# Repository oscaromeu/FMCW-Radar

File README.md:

# Advise

The FMCW radar project is a very exciting project but it has many difficulties. First of
all, it is a project that requires a long time since it involves many aspects of electrical engineering and takes many steps to build a prototype. Ideally, you should start with a modular approach, test all the modules
separately and then join them in a final design. To carry out this project ideally it should be done between three people in this way the signal processing part could be included. RF is a very exciting field but depending the project doing at your home will be very difficult because as we rise the frequency the equipment gets very expensive. If you want to make a Radar or do some stuff related to radio frequency: SDR, Radio Receivers/Transmitters, Antennas, ...  take a look at the following sources:

+ [University of California EEC134](https://github.com/ucdart/UCD-EEC134)
+ [Third version of homemade 6 GHz FMCW Radar](https://hforsten.com/third-version-of-homemade-6-ghz-fmcw-radar.html)
+ [ARRL Handbook](http://www.arrl.org/arrl-handbook-2019)

This repo is for remember myself that I was able to make a radar with the aid of my bachelor thesis supervisor. Thank you Javier, this project would not have been the same without your wisdom and your hands on expertise. :)

# FMCW-RADAR Project

The primary purpose of this project was to design and implement an Frequency Modulated Continous Wave Radar (FMCW) system centered at 5.8 GHz which can perform range, Doppler,
and synthetic aperture radar (SAR) measurements. The project was done with a modular design
approach and it had the following deliverables

+ RF front end board
+ Tx/Rx Antennas both Vivaldi type

## Target Audience 

The target audience of this project encompasses educational institutions or any individual
afiliated or not to any educational institution. All of the outputs of the project has a MIT License and are avaible at github. 

## Architecture general overview

A homodyne receiver is selected due to its small size and low parts count. In the following figure we
have a basic diagram of the radar system. In green we have the transmitter path and in red
we have the receiver path.

img//experimental-setup-1.jpg
## General overview of the results

### Vivaldi Antenna

Usually radars use very directional horn antennas. Directionality of the beam is important
so that only signal from the target is picked up instead of the surroundings. Besides the
directionality radar antenna should have low sidebands so that antenna to antenna coupling
is low and it doesn’t pick up reflected signals from behind and sides of the radar. 
Maybe a pyramidal horn antenna would be a good choice it can fulfill all the specifications
but it has high cost. Another option was Patch antenna but it was discarted due to it has a
low fractional bandwidth.
Finally, we decided to made a Vivaldi antenna. Vivaldi antennas are useful for any frequency, as all antennas are scalable in size for use at any frequency. Printed circuit technology
makes this type antenna cost effective at microwave frequencies exceeding 1 GHz.

The substrate of the antenna vivaldi was chosen
as a low cost FR4 material of thickness 1.2 mm. This was an error since the simulation was
done with a thickness of 0.8mm. The third antenna was fabricated with a thickness of 0.8mm. For this antenna the experimental data fits better with the simulation.

### Bottom 

### Top

### Experimental Results compared with simulation ones.

</br> </br> 
As we can see in the previous figure the reflection coefficient at the input relative to 50-ohm reference
impedance is below -10 dB for the frequency range from 3.1 GHz to 11 GHz.

## Radar board results

The radar test board is the last step of the test phase.  Prior to that a modular test approach was followed to verify that every component of the radar worked as expected. In the following figure is shown the final PCB of the radar system. In this stage it was encountered that the footprint of the VCO was not correct. Due to this the test applied to the radar was difficult
and hence the results are poor.

## Experimental Results 

</br> </br>

</br> </br>

####  A. Spectrum of the output signal before going to the transmitter antenna

#### B. Spectrum of the output of the mixer

The output of the Mixer is shown in Figure B. As is shown the baseband spectrum is
centered approximately at 44MHz and it has -22dB of power. This signal was acquired directly
with the aid of an active probe at the output of the Mixer. The signal that was being sent
with transmitter antenna is shown in Figure A.

## Some Future Ideas

+ Change the center frequency of 5GHz to 2.4GHz. 
+ Change the Wilkinson Divider for Coupler divider design. This could give us the flexibility to redistribute the power.
+ A 4 layer layout design is better option to design the radar since this way we separate
the signal layer with power and ground layer.
+ Process the IF signal with the aid of a microcontroller. Before processing the signal 
with a microcontroller a base band signal board has to be done in order to accomodate
the signal to the input ADC of the microcontroller.

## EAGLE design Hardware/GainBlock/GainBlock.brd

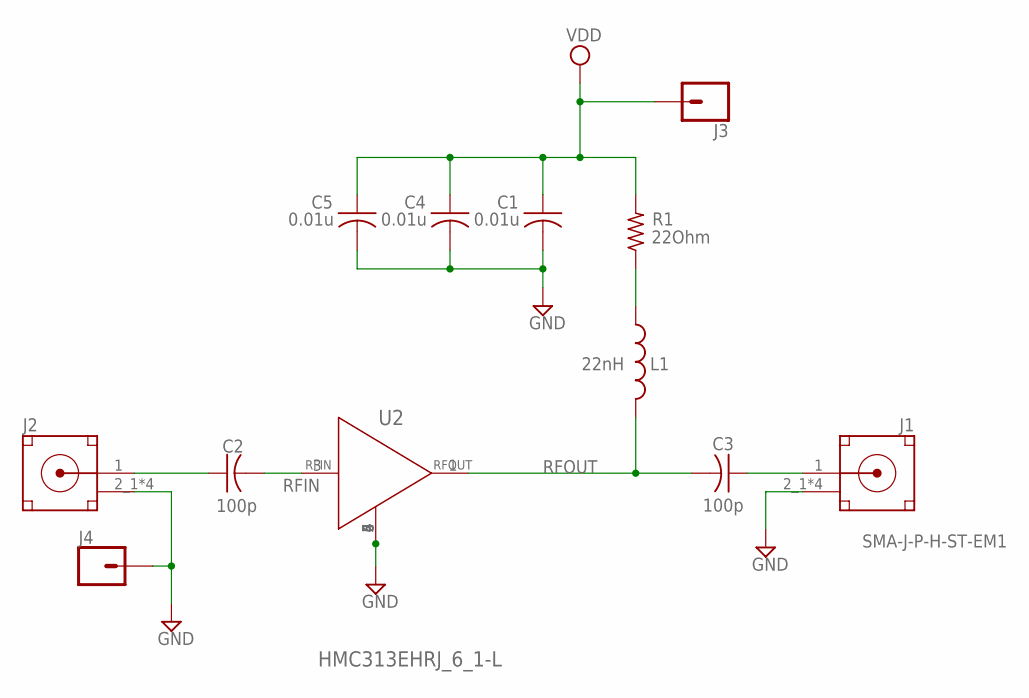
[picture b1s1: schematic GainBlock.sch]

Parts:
C1, C4, C5: 0.01u; C0805
C2, C3: 100p; C0805
J1, J2: SMA-J-P-H-ST-EM1
J3, J4: CONN_01; 1X01
L1: 22nH; L0805
R1: 22Ohm; R0805
U2: HMC313EHRJ_6_1-L; HRJ_6_1-L

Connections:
GND: C1.2, C4.2, C5.2, J1.2_1 (GND), J1.2_2 (GND), J1.3_1 (GND), J1.3_2 (GND), J2.2_1 (GND), J2.2_2 (GND), J2.3_1 (GND), J2.3_2 (GND), J4.1, U2.2 (GND_2), U2.4 (GND_3), U2.5 (GND_4), U2.6 (GND)
unnamed: C2.1, J2.1 (SIGNAL)
unnamed: C3.1, J1.1 (SIGNAL)
unnamed: L1.1, R1.1
RFIN: C2.2, U2.3 (RFIN)
RFOUT: C3.2, L1.2, U2.1 (RFOUT)
VDD: C1.1, C4.1, C5.1, J3.1, R1.2

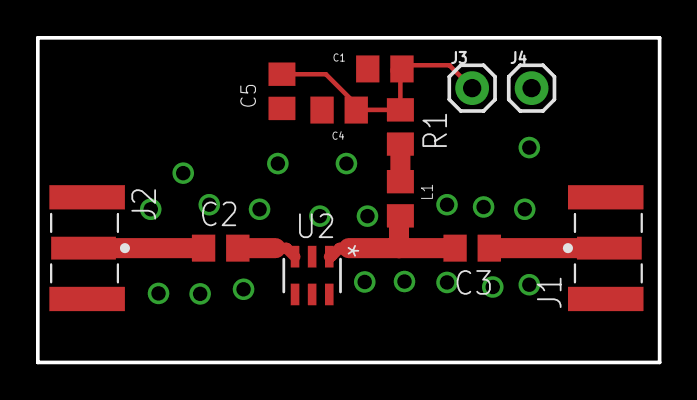
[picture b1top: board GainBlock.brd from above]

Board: 2 copper layers, 34.5 x 18.0 mm, 12 parts (0 on the bottom side), 7 nets.

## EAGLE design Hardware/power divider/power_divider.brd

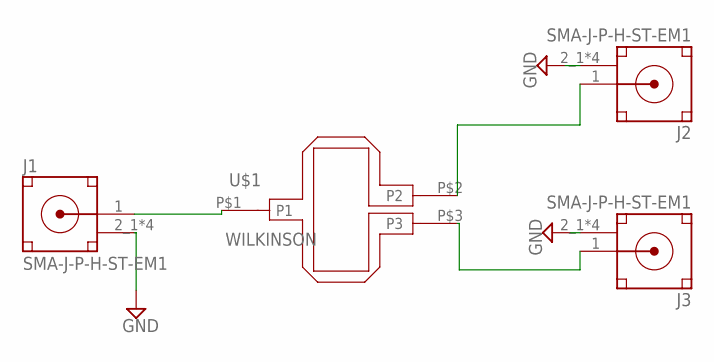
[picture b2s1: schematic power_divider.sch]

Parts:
J1, J2, J3: SMA-J-P-H-ST-EM1
U$1: WILKINSON

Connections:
GND: J1.2_1 (GND), J1.2_2 (GND), J1.3_1 (GND), J1.3_2 (GND), J2.2_1 (GND), J2.2_2 (GND), J2.3_1 (GND), J2.3_2 (GND), J3.2_1 (GND), J3.2_2 (GND), J3.3_1 (GND), J3.3_2 (GND)
unnamed: J1.1 (SIGNAL), U$1.P$1 (P1)
unnamed: J2.1 (SIGNAL), U$1.P$2 (P2)
unnamed: J3.1 (SIGNAL), U$1.P$3 (P3)

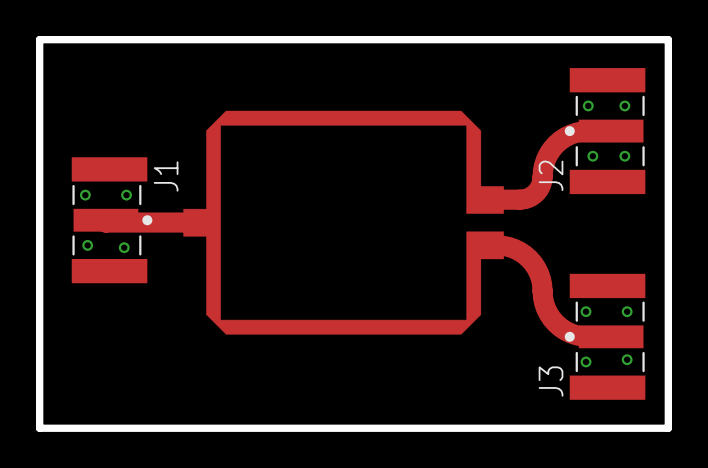
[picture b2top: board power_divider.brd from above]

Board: 2 copper layers, 34.9 x 21.6 mm, 4 parts (0 on the bottom side), 4 nets.

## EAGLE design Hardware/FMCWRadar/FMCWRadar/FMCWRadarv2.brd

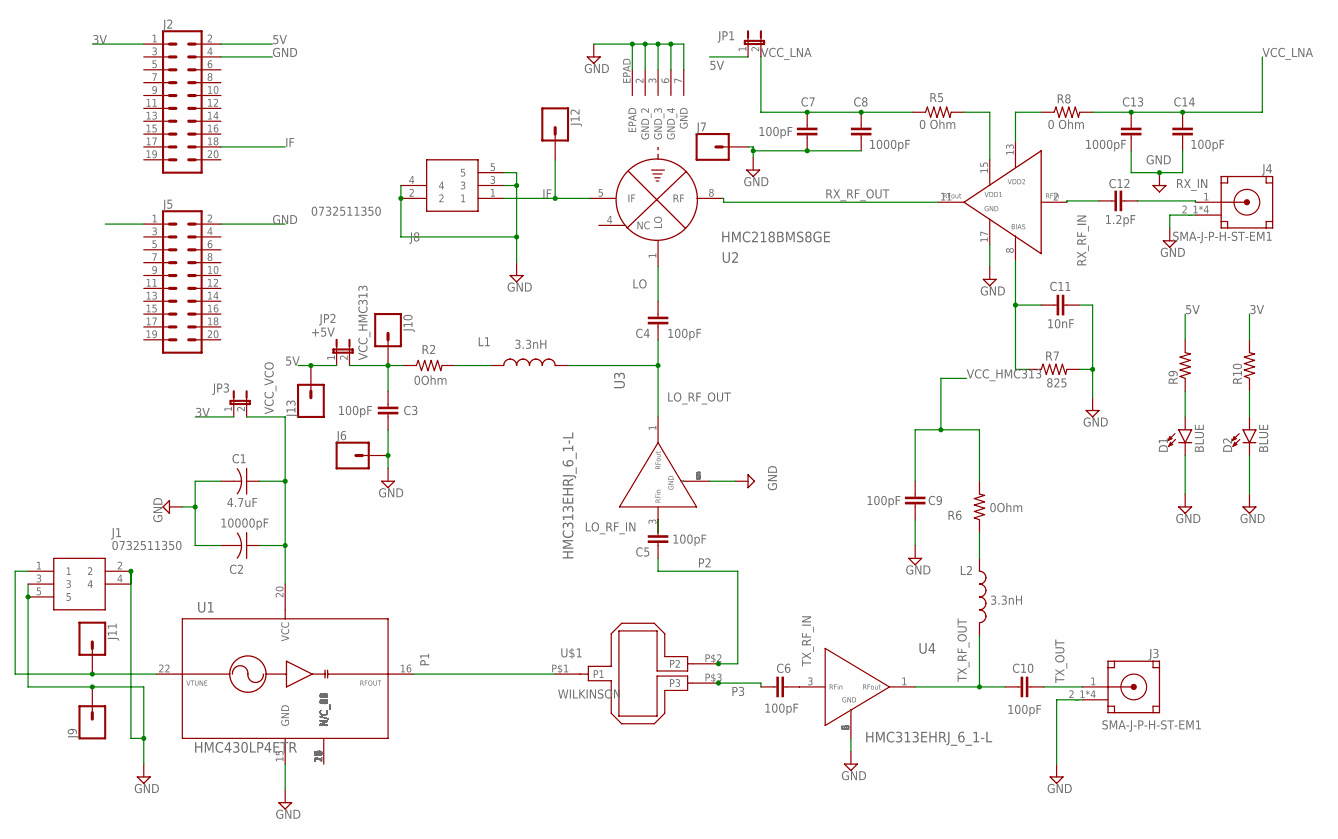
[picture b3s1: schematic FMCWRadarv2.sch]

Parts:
C1: 4.7uF; C0805
C2: 10000pF; C0603
C3, C9: 100pF; C0805
C4, C5, C6, C10: 100pF; C0402
C7, C14: 100pF; C0603
C8, C13: 1000pF; C0603
C11: 10nF; C0402
C12: 1.2pF; C0402
D1, D2: BLUE; LED-1206
J1, J8: 0732511350
J2, J5: CONN_10X2; 2X10
J3, J4: SMA-J-P-H-ST-EM1
J6, J7, J9, J10, J11, J12, J13: CONN_01; 1X01
JP1, JP2, JP3: +5V; JP1M
L1, L2: 3.3nH; L0805
R2, R6: 0Ohm; R0805
R5, R8: 0 Ohm; R0402
R7: 825; R0402
R9, R10: R-US_R0805; R0805
U1: HMC430LP4ETR; SMT_24
U2: HMC218BMS8GE; HRH_8_1
U3, U4: HMC313EHRJ_6_1-L; HRJ_6_1-L
U5: HMC717ALP3E; QFN50P300X300X100-17N
U$1: WILKINSON

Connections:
3V: J2.1, JP3.1, R10.2
5V: J2.2, J13.1, JP1.1, JP2.1, R9.2
GND: C1.2, C2.2, C3.2, C7.2, C8.2, C9.2, C11.1, C13.2, C14.2, D1.C, D2.C, J1.2, J1.3, J1.4, J1.5, J2.4, J3.2_1 (GND), J3.2_2 (GND), J3.3_1 (GND), J3.3_2 (GND), J4.2_1 (GND), J4.2_2 (GND), J4.3_1 (GND), J4.3_2 (GND), J5.2, J6.1, J7.1, J8.2, J8.3, J8.4, J8.5, J9.1, R7.2, U1.15 (GND), U2.2 (GND_2), U2.3 (GND_3), U2.6 (GND_4), U2.7 (GND), U2.EPAD, U3.2 (GND_2), U3.4 (GND_3), U3.5 (GND_4), U3.6 (GND), U4.2 (GND_2), U4.4 (GND_3), U4.5 (GND_4), U4.6 (GND), U5.17 (GND)
IF: J2.18, J8.1, J12.1, U2.5 (IF)
LO: C4.2, U2.1 (LO)
LO_RF_IN: C5.2, U3.3 (RFIN)
LO_RF_OUT: C4.1, L1.2, U3.1 (RFOUT)
unnamed: R5.2, U5.15 (VDD1)
unnamed: R8.1, U5.13 (VDD2)
unnamed: C11.2, R7.1, U5.8 (BIAS)
unnamed: J1.1, J11.1, U1.22 (VTUNE)
unnamed: D1.A, R9.1
unnamed: D2.A, R10.1
unnamed: L2.1, R6.1
unnamed: L1.1, R2.2
P1: U1.16 (RFOUT), U$1.P$1 (P1)
P2: C5.1, U$1.P$2 (P2)
P3: C6.1, U$1.P$3 (P3)
RX_IN: C12.1, J4.1 (SIGNAL)
RX_RF_IN: C12.2, U5.2 (RFIN)
RX_RF_OUT: U2.8 (RF), U5.11 (RFOUT)
TX_OUT: C10.2, J3.1 (SIGNAL)
TX_RF_IN: C6.2, U4.3 (RFIN)
TX_RF_OUT: C10.1, L2.2, U4.1 (RFOUT)
VCC_HMC313: C3.1, C9.1, J10.1, JP2.2, R2.1, R6.2
VCC_LNA: C7.1, C8.1, C13.1, C14.1, JP1.2, R5.1, R8.2
VCC_VCO: C1.1, C2.1, JP3.2, U1.20 (VCC)

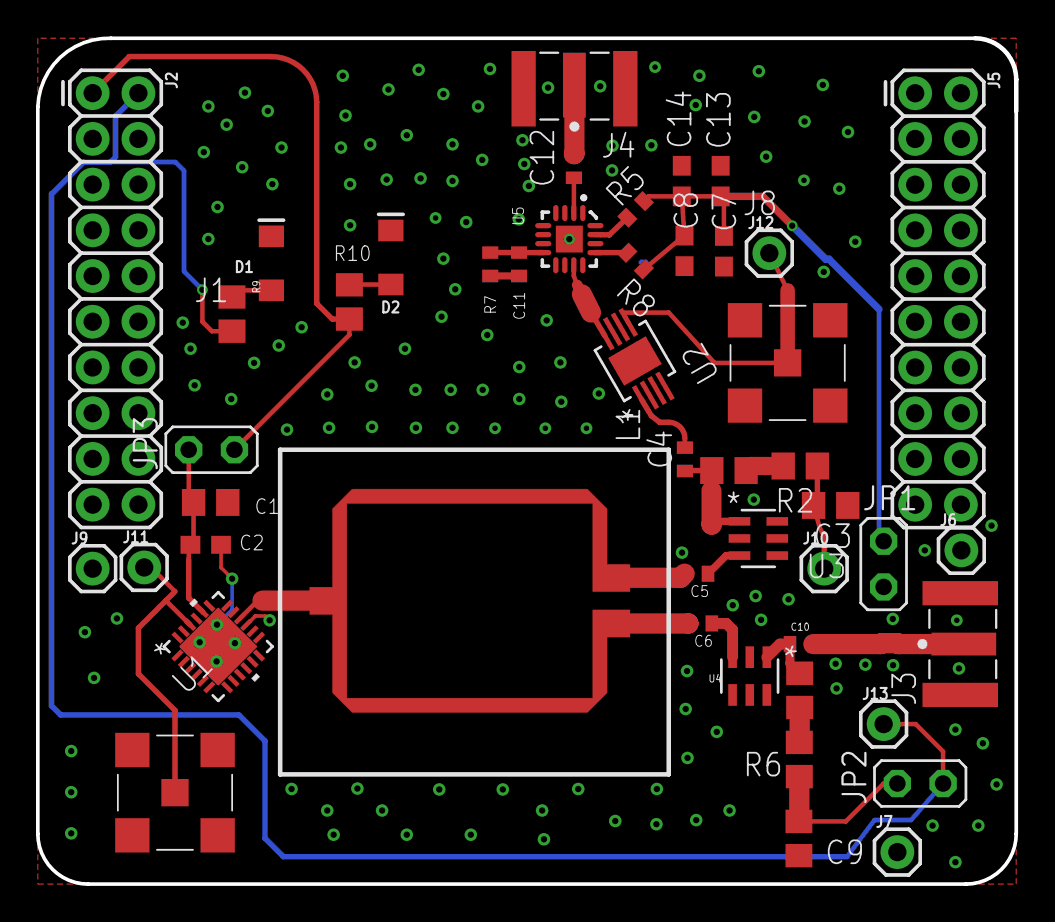
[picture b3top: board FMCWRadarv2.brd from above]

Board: 2 copper layers, 54.3 x 47.0 mm, 47 parts (0 on the bottom side), 27 nets.

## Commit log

2021-03-11 added FMCW Radar Project
2021-03-11 Fix README.md

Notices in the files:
parts and their libraries:
SparkFun-LED: Licensing: Creative Commons ShareAlike 4.0 International - https://creativecommons.org/licenses/by-sa/4.0
